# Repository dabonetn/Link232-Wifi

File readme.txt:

Usage Notes

BBS Host Mode.
The current BBS host mode enables a local echo by default, so to make it actually work with bbs software, when you enable
bbs host in the at+config menu, in the bbs host submenu, make sure echo is set to off.

128 Users. I noticed on DESTERM and Dialogue 128, that if you have the modem set to hangup on DTR drop,
the modem will hang up trying to download. To disable this function, enter the command
ats54=2 then press enter, then at&w then enter to save it to the modem.
After this, you have to use the +++, wait and then ATH for hangup on your side.

Main Readme.

Link232-Wifi, Swift-L and Swift-T

This project covers the Link232 and Swiftlink RS232 carts combined with the zimodem firmware.
It has my Cartridge version, along with the Internal Versions for the 128, 128DCR and C64 longboard.

Link232-Wifi
This is a Swiftlink compatible High Speed Uart cartridge for the Commodore 64/128.
Because it's a link232 clone, it only uses 16 bytes of the dXXX address space, and you can set it using the solder jumpers. 
You must cut the dx00 link and then connect the solder jumper you want the new address to be.

Swift-T
This is a Swiftlink compatible internal wifi modem for the c64 longboard and the 128DCR.
It plugs into a socket at U2 and then you install the 6526 into the modem board.
Flying leads then connect the IO address (DE00 or DF00) and Dotclock.
On the 128DCR, it plugs in U1, and has one more flying lead to connect the NMI line. (Total of 3)

Swift-L
This is a Swiftlink compatible internal wifi modem for the C128 flat model.
It plugs into a socket at U2 and then you install the 6526 into the modem board.
Flying leads then connect the IO address (DE00/DF00/Or D700) and Dotclock.

All of them use swiftlink drivers in your favorite terminal program/bbs.
CCGMS/Novaterm/Desterm/etc.. 

For Centipede 128 BBS software, new Swiftlink drivers for address DF00 and D700 are located under the SoftwarePatches directory.
(It only had DE00 by default)

Premade units are usually available on ebay from me.

https://www.ebay.com/sch/tndabone/m.html?_nkw=&_armrs=1&_ipg=&_from=

Default for most programs is DE00/NMI

Modem commands are under the Zimodem directory.

I'm merging the Internal Units and the Cartridge version under this page. As all 3 use the same firmware.

Much thanks to Dr. Evil Laboratories for designing the original Swiftlink Cart.
And to Jim Brain for the Link232 design,
And of course Bo Zimmerman for the very excellent Zimodem firmware.

Please see the quick start guide if you bought a prebuilt cart.

Default setting for a new unit from me is.

DE00/NMI

19200 Baud
Hardware Flow Control (CTS/RTS)

The current zimodem firmware is forked from version "3.7.0"

To update to the current firmware use the command

at&u6502

For usage of zimodem, see the readme in the zimodem directory.
Link232-Wifi is based off the ESP-12, not the ESP32, so No esp32 only features will work.

Changes I've made.

In Zimodem.ino I've set 19200 baud as standard, and got rid of the signal inversion while using a ESP8266 module.

Zcommand.ino mainly has me replacing the zimmers.net with dabone.xyz to prevent a update and bricking of the Link232-Wifi.
Telnet protocol on atdt dialing has been disabled by default ""telnetSupport=false;""
To renable telnet translation by the modem instead of the terminal, use the command ats62=1.

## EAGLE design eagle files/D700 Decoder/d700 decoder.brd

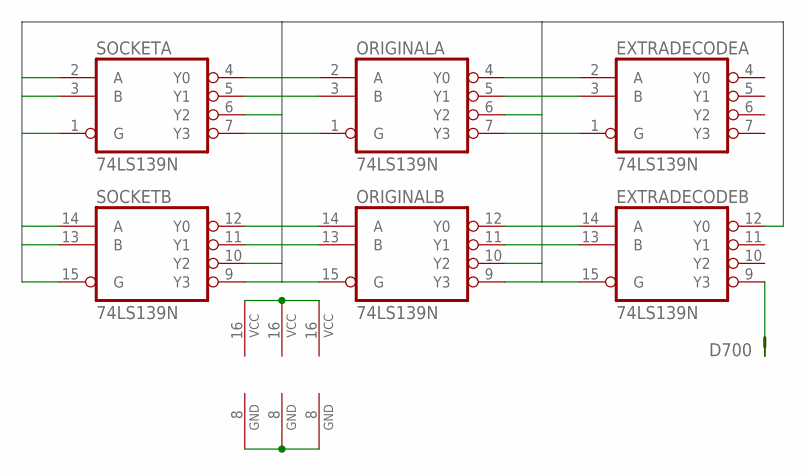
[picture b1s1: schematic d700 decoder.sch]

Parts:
D700: TP; JP1
EXTRADECODE: 74LS139N; DIL16
ORIGINAL: 74LS139N; DIL16
SOCKET: 74LS139N; DIL16

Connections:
A(2): EXTRADECODE.2 (A), ORIGINAL.2 (A), SOCKET.2 (A)
A(14): EXTRADECODE.14 (A), ORIGINAL.14 (A), SOCKET.14 (A)
B(3): EXTRADECODE.3 (B), ORIGINAL.3 (B), SOCKET.3 (B)
B(13): EXTRADECODE.13 (B), ORIGINAL.13 (B), SOCKET.13 (B)
G(1): EXTRADECODE.1 (G), ORIGINAL.1 (G), SOCKET.1 (G)
G(15): ORIGINAL.15 (G), SOCKET.15 (G)
GND: EXTRADECODE.8 (GND), ORIGINAL.8 (GND), SOCKET.8 (GND)
unnamed: D700.1, EXTRADECODE.9 (Y3)
SIDINTERNAL: EXTRADECODE.15 (G), ORIGINAL.5 (Y1)
VCC: EXTRADECODE.16 (VCC), ORIGINAL.16 (VCC), SOCKET.16 (VCC)
Y0(4-VICOUT): ORIGINAL.4 (Y0), SOCKET.4 (Y0)
Y0(12): ORIGINAL.12 (Y0), SOCKET.12 (Y0)
Y1(5-SIDOUT): EXTRADECODE.12 (Y0), SOCKET.5 (Y1)
Y1(11): ORIGINAL.11 (Y1), SOCKET.11 (Y1)
Y2(6): ORIGINAL.6 (Y2), SOCKET.6 (Y2)
Y2(10): ORIGINAL.10 (Y2), SOCKET.10 (Y2)
Y3(7): ORIGINAL.7 (Y3), SOCKET.7 (Y3)
Y3(9): ORIGINAL.9 (Y3), SOCKET.9 (Y3)

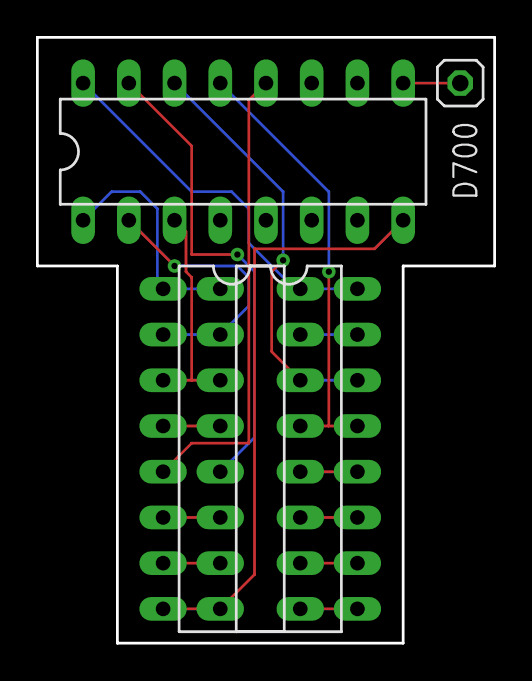
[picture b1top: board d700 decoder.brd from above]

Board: 2 copper layers, 25.4 x 33.7 mm, 4 parts (0 on the bottom side), 18 nets.

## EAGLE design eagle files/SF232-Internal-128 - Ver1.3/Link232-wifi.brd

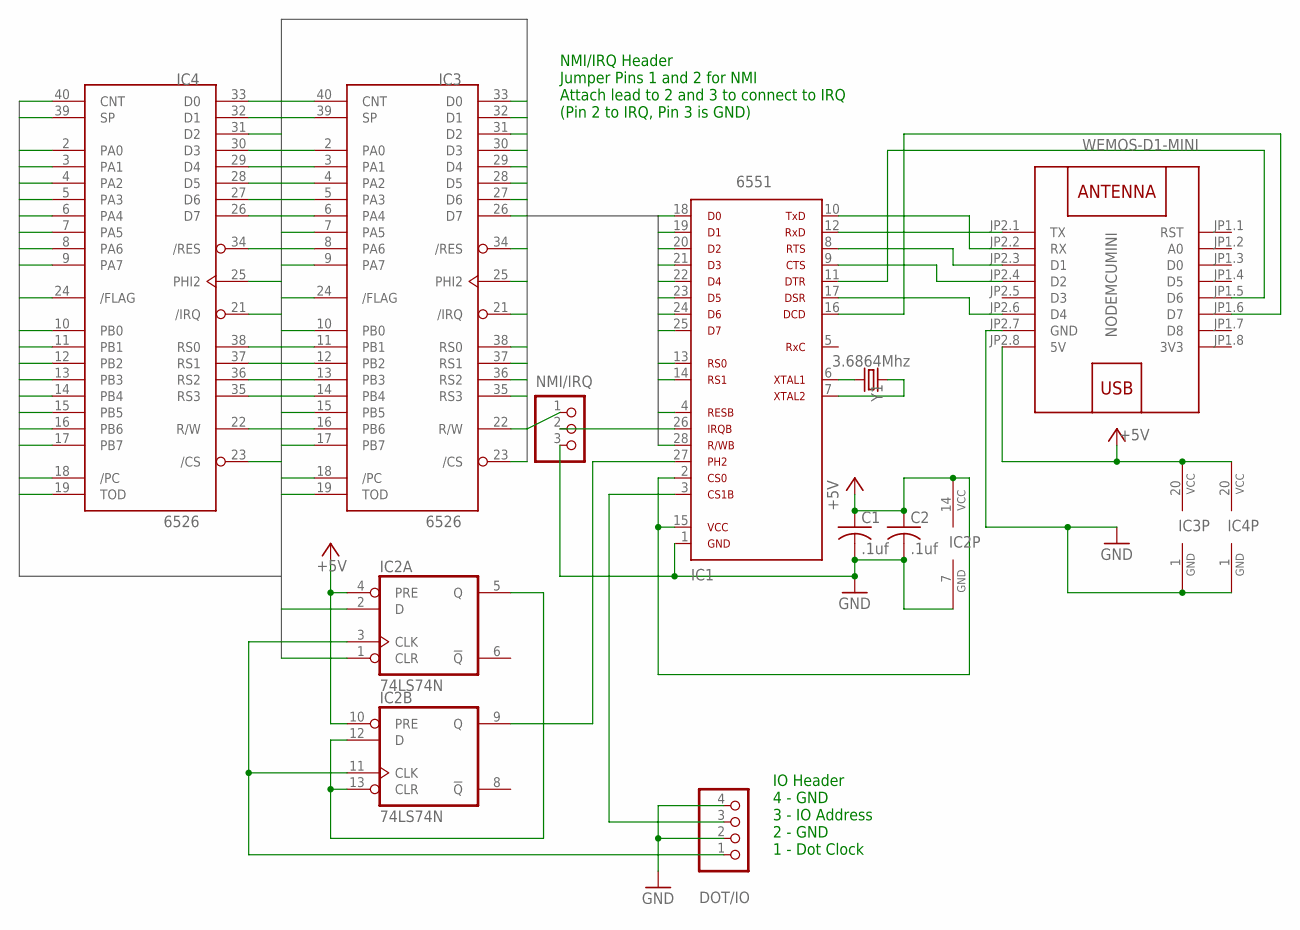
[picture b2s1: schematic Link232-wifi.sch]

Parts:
C1, C2: .1uf; C050-024X044
DOT/IO: PINHD-1X4; 1X04
IC1: 6551
IC2: 74LS74N; DIL14
IC3, IC4: 6526; DIP40
JP1: NMI/IRQ; 1X03
NODEMCUMINI: WEMOS-D1-MINI
Y1: 3.6864Mhz; HC49US

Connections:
3V3: NODEMCUMINI.JP1.8 (3V3)
+5V: C1.1, C2.1, IC1.2, IC1.15, IC2.4 (PRE), IC2.10 (PRE), IC2.14 (VCC), IC3.20 (VCC), IC4.20 (VCC), NODEMCUMINI.JP2.8 (5V)
/CS: IC3.23 (/CS), IC4.23 (/CS)
/FLAG: IC3.24 (/FLAG), IC4.24 (/FLAG)
/PC: IC3.18 (/PC), IC4.18 (/PC)
CNT: IC3.40 (CNT), IC4.40 (CNT)
D0: IC1.18, IC3.33 (D0), IC4.33 (D0)
D1: IC1.19, IC3.32 (D1), IC4.32 (D1)
D2: IC1.20, IC3.31 (D2), IC4.31 (D2)
D3: IC1.21, IC3.30 (D3), IC4.30 (D3)
D4: IC1.22, IC3.29 (D4), IC4.29 (D4)
D5: IC1.23, IC3.28 (D5), IC4.28 (D5)
D6: IC1.24, IC3.27 (D6), IC4.27 (D6)
D7: IC1.25, IC3.26 (D7), IC4.26 (D7)
GND: C1.2, C2.2, DOT/IO.2, DOT/IO.4, IC1.1, IC2.7 (GND), IC3.1 (GND), IC4.1 (GND), JP1.3, NODEMCUMINI.JP2.7 (GND)
IRQ: IC3.21 (/IRQ), IC4.21 (/IRQ), JP1.1
unnamed: DOT/IO.1, IC2.3 (CLK), IC2.11 (CLK)
unnamed: IC2.5 (Q), IC2.12 (D), IC2.13 (CLR)
unnamed: IC1.27, IC2.9 (Q)
unnamed: IC1.26, JP1.2
unnamed: DOT/IO.3, IC1.3
unnamed: IC1.6, Y1.2
unnamed: IC1.7, Y1.1
unnamed: IC1.12, NODEMCUMINI.JP2.1 (TX)
unnamed: IC1.10, NODEMCUMINI.JP2.2 (RX)
unnamed: IC1.8, NODEMCUMINI.JP2.3 (D1)
unnamed: IC1.9, NODEMCUMINI.JP2.4 (D2)
unnamed: IC1.17, NODEMCUMINI.JP2.6 (D4)
unnamed: IC1.11, NODEMCUMINI.JP1.5 (D6)
unnamed: IC1.16, NODEMCUMINI.JP1.6 (D7)
PA0: IC3.2 (PA0), IC4.2 (PA0)
PA1: IC3.3 (PA1), IC4.3 (PA1)
PA2: IC3.4 (PA2), IC4.4 (PA2)
PA3: IC3.5 (PA3), IC4.5 (PA3)
PA4: IC3.6 (PA4), IC4.6 (PA4)
PA5: IC3.7 (PA5), IC4.7 (PA5)
PA6: IC3.8 (PA6), IC4.8 (PA6)
PA7: IC3.9 (PA7), IC4.9 (PA7)
PB0: IC3.10 (PB0), IC4.10 (PB0)
PB1: IC3.11 (PB1), IC4.11 (PB1)
PB2: IC3.12 (PB2), IC4.12 (PB2)
PB3: IC3.13 (PB3), IC4.13 (PB3)
PB4: IC3.14 (PB4), IC4.14 (PB4)
PB5: IC3.15 (PB5), IC4.15 (PB5)
PB6: IC3.16 (PB6), IC4.16 (PB6)
PB7: IC3.17 (PB7), IC4.17 (PB7)
PHI2: IC2.1 (CLR), IC2.2 (D), IC3.25 (PHI2), IC4.25 (PHI2)
RES: IC1.4, IC3.34 (/RES), IC4.34 (/RES)
RS0: IC1.13, IC3.38 (RS0), IC4.38 (RS0)
RS1: IC1.14, IC3.37 (RS1), IC4.37 (RS1)
RS2: IC3.36 (RS2), IC4.36 (RS2)
RS3: IC3.35 (RS3), IC4.35 (RS3)
RW: IC1.28, IC3.22 (R/W), IC4.22 (R/W)
SP: IC3.39 (SP), IC4.39 (SP)
TOD: IC3.19 (TOD), IC4.19 (TOD)

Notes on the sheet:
IO Header 4 - GND 3 - IO Address 2 - GND 1 - Dot Clock
NMI/IRQ Header Jumper Pins 1 and 2 for NMI Attach lead to 2 and 3 to connect to IRQ (Pin 2 to IRQ, Pin 3 is GND)

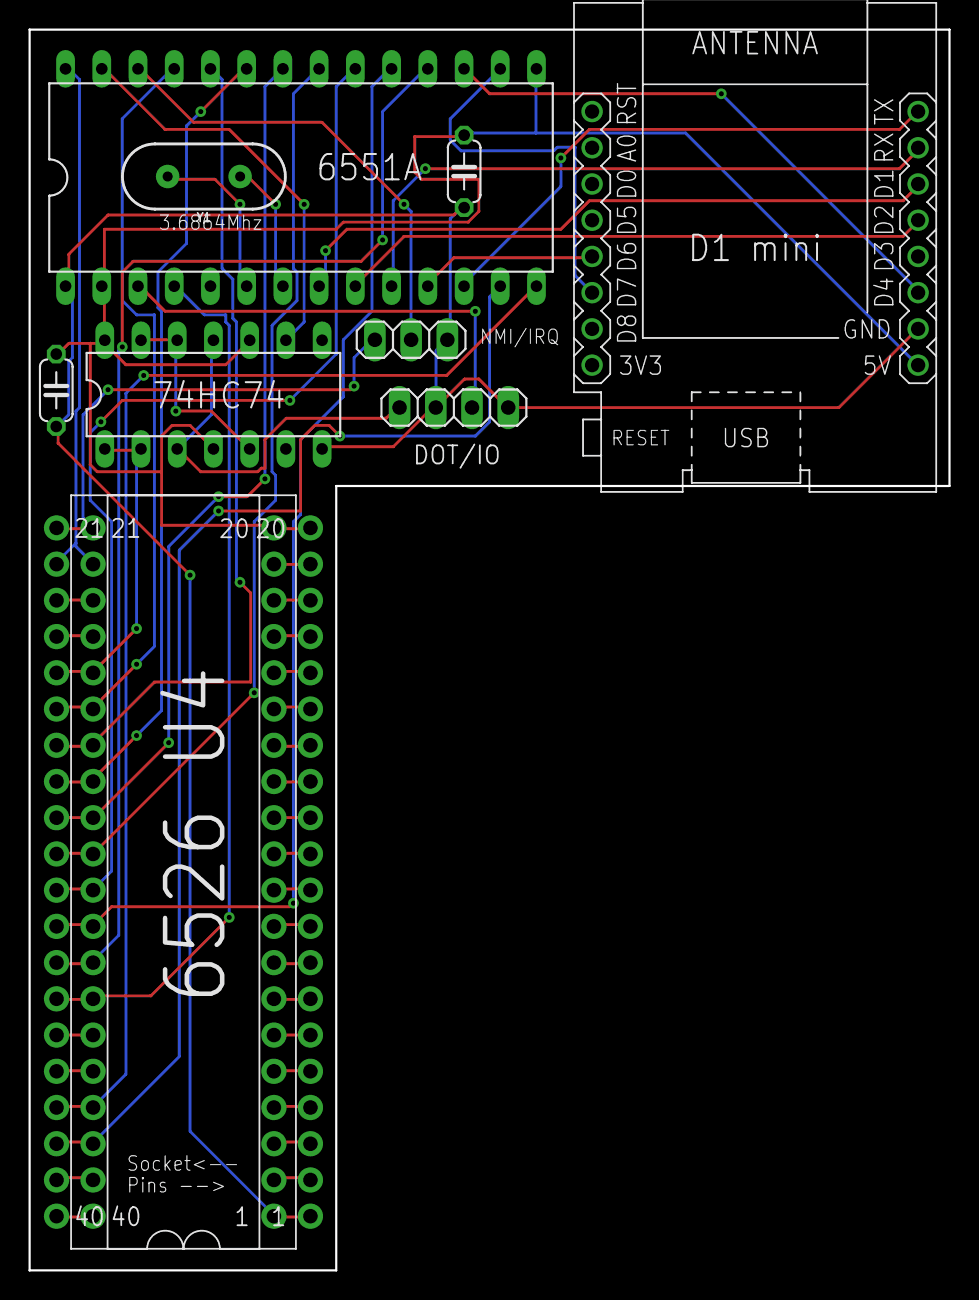
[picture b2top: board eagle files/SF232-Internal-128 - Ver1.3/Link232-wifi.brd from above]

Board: 2 copper layers, 64.5 x 87.0 mm, 10 parts (0 on the bottom side), 54 nets.

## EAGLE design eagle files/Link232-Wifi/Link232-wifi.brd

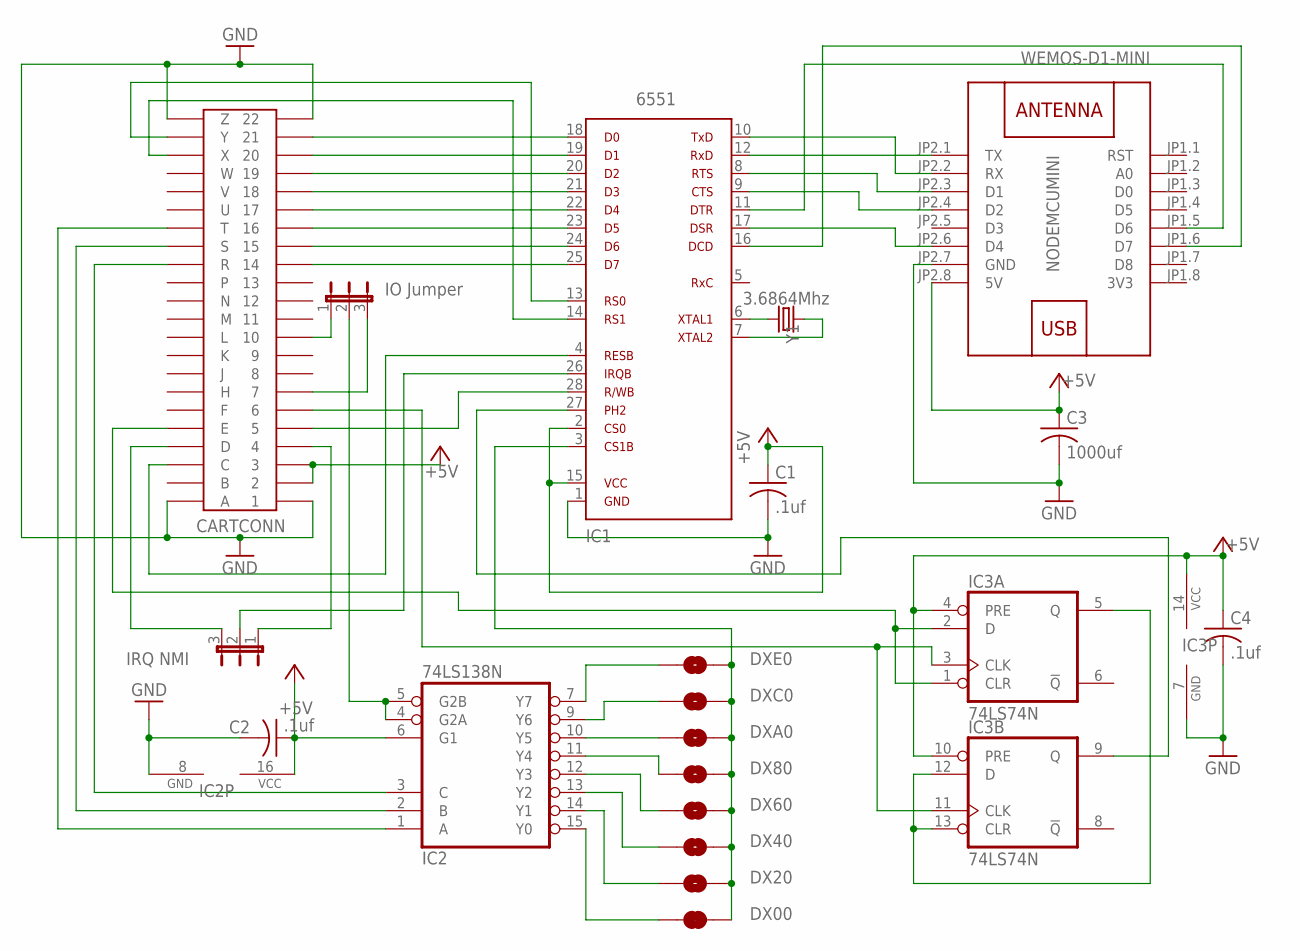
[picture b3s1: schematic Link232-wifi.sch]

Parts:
C1, C2, C4: .1uf; C050-024X044
C3: 1000uf; C050-024X044
CARTCONN: 44PINEDGE
DF/DE: IO Jumper; JP2
DX00: JUMPER-SMT_2_NC_TRACE_SILK; SMT-JUMPER_2_NC_TRACE_SILK
DX20, DX40, DX60, DX80: JUMPER-SMT_2_NO_SILK; SMT-JUMPER_2_NO_SILK
DXA0: JUMPER-SMT_2_NO_SILK; SMT-JUMPER_2_NO_SILK
DXC0: JUMPER-SMT_2_NO_SILK; SMT-JUMPER_2_NO_SILK
DXE0: JUMPER-SMT_2_NO_SILK; SMT-JUMPER_2_NO_SILK
IC1: 6551A; 6551
IC2: 74LS138N; DIL16
IC3: 74LS74N; DIL14
IRQ/NMI: IRQ NMI; JP2
NODEMCUMINI: WEMOS-D1-MINI
Y1: 3.6864Mhz; HC49US

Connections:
3V3: NODEMCUMINI.JP1.8 (3V3)
+5V: C1.1, C2.1, C3.1, C4.1, CARTCONN.2, CARTCONN.3, IC1.2, IC1.15, IC2.6 (G1), IC2.16 (VCC), IC3.4 (PRE), IC3.10 (PRE), IC3.14 (VCC), NODEMCUMINI.JP2.8 (5V)
GND: C1.2, C2.2, C3.2, C4.2, CARTCONN.1, CARTCONN.22, CARTCONN.A, CARTCONN.Z, IC1.1, IC2.8 (GND), IC3.7 (GND), NODEMCUMINI.JP2.7 (GND)
unnamed: CARTCONN.6, IC3.3 (CLK), IC3.11 (CLK)
unnamed: IC3.5 (Q), IC3.12 (D), IC3.13 (CLR)
unnamed: IC1.27, IC3.9 (Q)
unnamed: CARTCONN.21, IC1.18
unnamed: CARTCONN.20, IC1.19
unnamed: CARTCONN.19, IC1.20
unnamed: CARTCONN.18, IC1.21
unnamed: CARTCONN.17, IC1.22
unnamed: IC1.6, Y1.2
unnamed: IC1.7, Y1.1
unnamed: IC1.12, NODEMCUMINI.JP2.1 (TX)
unnamed: IC1.10, NODEMCUMINI.JP2.2 (RX)
unnamed: IC1.8, NODEMCUMINI.JP2.3 (D1)
unnamed: IC1.9, NODEMCUMINI.JP2.4 (D2)
unnamed: IC1.17, NODEMCUMINI.JP2.6 (D4)
unnamed: IC1.11, NODEMCUMINI.JP1.5 (D6)
unnamed: IC1.16, NODEMCUMINI.JP1.6 (D7)
unnamed: CARTCONN.5, IC1.28
unnamed: CARTCONN.C, IC1.4
unnamed: CARTCONN.D, IRQ/NMI.3
unnamed: CARTCONN.E, IC3.1 (CLR), IC3.2 (D)
unnamed: CARTCONN.10, DF/DE.1
unnamed: CARTCONN.7, DF/DE.3
unnamed: DF/DE.2, IC2.4 (G2A), IC2.5 (G2B)
unnamed: CARTCONN.T, IC2.1 (A)
unnamed: CARTCONN.S, IC2.2 (B)
unnamed: CARTCONN.R, IC2.3 (C)
unnamed: CARTCONN.X, IC1.14
unnamed: CARTCONN.Y, IC1.13
unnamed: DXE0.1, IC2.7 (Y7)
unnamed: CARTCONN.4, IRQ/NMI.1
unnamed: DXC0.1, IC2.9 (Y6)
unnamed: DXA0.1, IC2.10 (Y5)
unnamed: DX80.1, IC2.11 (Y4)
unnamed: DX60.1, IC2.12 (Y3)
unnamed: DX40.1, IC2.13 (Y2)
unnamed: DX20.1, IC2.14 (Y1)
unnamed: DX00.1, IC2.15 (Y0)
unnamed: DX00.2, DX20.2, DX40.2, DX60.2, DX80.2, DXA0.2, DXC0.2, DXE0.2, IC1.3
unnamed: CARTCONN.16, IC1.23
unnamed: IC1.26, IRQ/NMI.2
unnamed: CARTCONN.15, IC1.24
unnamed: CARTCONN.14, IC1.25

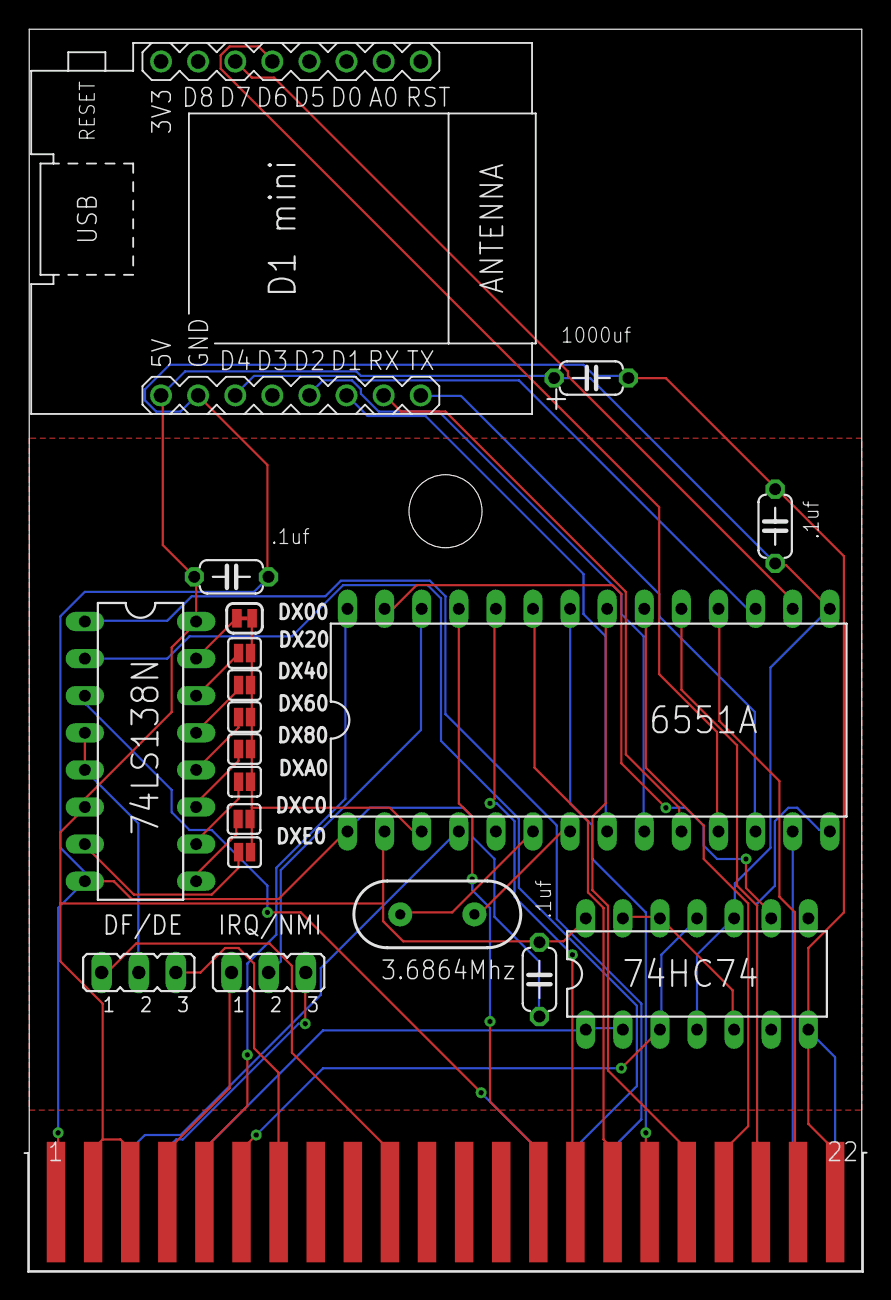
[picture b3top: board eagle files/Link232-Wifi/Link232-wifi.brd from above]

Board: 2 copper layers, 57.0 x 85.0 mm, 20 parts (0 on the bottom side), 45 nets.

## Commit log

2020-08-01 Moving to Non Forked Copy of Zimodem
2020-08-02 Sync And Fixes
    Sync to Zimodem release as of (08-01-2020).
    Fixed the following bugs.
    DCD wasn't being raised if the connection was made using the ATA command.
    When CTS/RTS is enabled on the Link232-Wifi, the NO CARRIER response for the modem was cut off after 2 characters.
2020-08-02 Sync And Fixes (2)
    Sync to Zimodem release as of (08-01-2020). For real this time.. oops.
    Fixed the following bugs.
    DCD wasn't being raised if the connection was made using the ATA command.
    When CTS/RTS is enabled on the Link232-Wifi, the NO CARRIER response for the modem was cut off after 2 characters.
2020-09-14 Update Quickstart
    Update Quickstart
2020-12-29 Upgrade to Zimodem 3.5.6
    Upgrade to zimodem 3.5.6
    Includes stream fix by Fix broken up sending of escape sequences by hanshuebner.
    Also has DCD fix on manual answer fix.
2021-02-05 Create Link232-Manual-Firmware-Update.pdf
    Added Manual Firmware update instructions.
2021-02-07 Update Link232-Manual-Firmware-Update.pdf
    Clarify a couple of steps.
2021-07-02 Updated to Zimodem 3.6.3
2021-07-12 Update Link232-Manual-Firmware-Update.pdf
    Updated manual firmware to reflect need for 2.7.4 Libs
2021-11-23 Delete Link232-Wifi-cartridge-bottom.stl
    Incorrect model.
2022-04-02 Corrected docs for firmware settings
2022-05-20 Internal Modem directories renamed.
2022-05-21 Upgrade to Zimodem 3.7.0
    Upgrade to zimodem firmware 3.7.0.
    Disables telnet protocol by default on atdt dialing.
    Also added swiftlink compatible c64 programs under the cbm8bit directories.
2023-01-13 Updated Driver Notes
2023-02-21 Updated Docs
2023-03-09 Update readme.txt
    Add BBS Host echo notes.
2023-04-26 New Docs
    Added quick install guide for C128DCR.
2023-04-26 Fixed typo
2023-04-26 Added Centipede drivers for DF00/D700
    Added SoftwarePatches directory.
2023-05-07 Fixed typo.....
2023-05-08 Another typo.
2024-06-01 Update Link232-Manual-Firmware-Update.pdf
    Update download link

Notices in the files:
parts and their libraries:
SparkFun-Jumpers: Licensing: Creative Commons ShareAlike 4.0 International - https://creativecommons.org/licenses/by-sa/4.0
diy-modules: Released under the Creative Commons Attribution 4.0 International License: http://creativecommons.org/licenses/by/4.0
